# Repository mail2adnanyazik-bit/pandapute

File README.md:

# Pandapute - a mini computer built from scratch

Before you keep reading and find out more about my kickass project, first I want to give credit and a massive thanks to @zsharpminor, or Udo - He's my first friend on Hack Club, a reviewer, and all-around great guy who helped me with this project along every step of the way.
This project would not have been possible without him, so <3 to him :D

## The Inspiration

So, one day I was working on my Split Keyboard project at my makespace, and I saw a friend of mine using a cardputer adv (which is a small, portable esp-based computer - see pic), and was curious.
I asked him what it was, and he showed me, and I gotta say, I was skeptical at first, but then I was blown away - I just had one complaint when I saw the thing :
the keyboard. You see, the original cardputer uses this tiny ass 56-key keyboard, which is 1) too many keys in my opinion, and 2) extremely hard to type on.

So, I decided to make my own, and get funding from Outpost.

## The Features

So, the Pandapute features every single feature the Cardputer has + more !

It has :

- The best ESP32 chip that has wifi and bluetooth capabilities (ESP32-S3-WROOM-1-N16R8)
- an actual **extremely** low profile, compact, built in mechanical 32-key keyboard
- an Audio Jack
- A LiPo battery that will last ages
- a built in speaker
- a microphone
- exposed I2C, GPIO, Power, etc. Pins so you can connect external modules or breakout boards, like a secondary display
- A USB-C port for **both** flashing **and** charging
- a tilt sensor (to do cool stuff)
- a 2.8" display (around twice as big as the cardputer)

## The Build

The Cardputer is built from scratch by me, Panda

It features an entirely custom

### Schematic

#### Power

#### ESP

#### Audio

#### Display

#### Keyboard

#### Peripherals

and

### PCB

to visualize how this will look in real life, here are a few pics ! I only added the important components that you'll actually see, not the encoder chips and stuff :

Now you're probably wondering, will you just carry a PCB around ? OF COURSE NOT. But you know what I'm also not gonna do ?
Put it in some lame ass 3d printed case. That would be boring, inaccurate, and wouldn't feel good in my hands. So ... what's my solution for the

### Case ?

You see, instead of the usual 3d printed stuff, I've decided I'm going to use the full potential of my makespace and make
a custom wood case with a nice finish and accurate measurements after ordering the components, using my local wood workshop.

Another reason for the wood case is inaccuracy - what I mean by that is that some of my components have rather inaccurate measurements - the measurements I have currently on the PCB are only approximations for some components, for example my display :
Since there isn't a prebuilt footprint for this, I had to make my own version which is based on a user-made 3d model approximation of the same component - the downside of this is that it's not accurate.
For the PCB this is rather easy to fix - just order the components first and _then_ adjust the PCB after measuring the components with a digital caliper !

As to how the case will be assembled - it will be made up of 2 parts - One bottom shell which holds the PCB and has holes for the audio jack, USB-C port, and whatever else sticks out the side, and one Top Plate which has holes that the top components that should be exposed can poke through (screen, switches, keyboard, etc.)

To visualize how the entire thing will look, I made a CAD after @zsharpminor (my first friend on Hack Club, was a great help, if you're reading this tysm ! ) said it would be helpful for polish

I first made a model of the Bottom Shell :

Then of the Top part (with cool Panda logo, also thanks to zsharp's feedback - again, tysm for putting up with me zsharp !)

After that for visualization purposes I made an Assembly to show how it will look in the end :

If you want a better more interactive look at this case and how it's built, check out the Onshape document where I made it !

https://cad.onshape.com/documents/acd94843717f517182d6e668/w/23be4fdb216877c251d3e9a3/e/5f36188dd017400931f1858c?renderMode=0&uiState=6a65fce0e255515915538acc

## Firmware

The firmware is a full OS-like environment, not just a bunch of drivers. It runs on the Arduino framework with PlatformIO and gives you a desktop UI, terminal, text editor, file manager, and USB HID keyboard mode.

```
firmware/
├── platformio.ini               # dev + release builds (TFT_eSPI, SdFat)
├── include/
│   ├── config.h                 # all pin definitions
│   ├── kernel.h                 # OS kernel — app management, status bar
│   └── apps.h                   # app function declarations
└── src/
    ├── main.cpp                 # boots hardware + OS, main event loop
    ├── kernel.cpp               # app switching, status bar, event routing
    ├── apps/
    │   ├── desktop.cpp          # home screen — app grid launcher
    │   ├── terminal.cpp         # shell with commands (help, clear, echo, bat, reboot)
    │   ├── editor.cpp           # text editor — cursor, insert/delete, Ln/Col status
    │   ├── files.cpp            # SD card file browser
    │   ├── settings.cpp         # brightness, volume, USB mode toggles
    │   ├── piano.cpp            # keyboard piano — keys 1-8 play notes, octave shift
    │   ├── mic.cpp              # mic level visualizer — real-time bar graph
    │   └── tilt.cpp             # MPU6050 orientation — circle + dot + accel/gyro values
    ├── keyboard/                # 4×8 matrix scanner, debounce, HID keymap
    ├── display/                 # TFT_eSPI wrapper
    ├── audio/                   # I²S output + ES8311 codec + mic input
    ├── touch/                   # XPT2046 SPI touch with calibration
    ├── power/                   # IP5306 battery manager + ADC fallback
    ├── sd_card/                 # SdFat wrapper
    ├── usb_hid/                 # USB HID keyboard — plug in and type
    └── mpu/                     # MPU6050 accelerometer + gyroscope driver
```

#### OS Architecture

The **kernel** manages 8 apps and a persistent status bar. Every keypress is routed to the currently focused app. The loop runs at ~100 Hz:

1. **Keyboard** — matrix scan → debounce → HID keycode lookup
2. **USB HID** — if connected to a computer, sends the same keystrokes
3. **App** — keypress fed to current app's `on_key()` handler
4. **Touch** — polls XPT2046 for touch position
5. **Battery** — reads IP5306 every 10s, shows in status bar
6. **Status bar** — redrawn every 200ms with app name + battery %
7. **Sensors** — MPU6050 and microphone polled by their respective apps

#### Apps

| App      | Icon | What it does                                                     |
| -------- | ---- | ---------------------------------------------------------------- |
| Desktop  | ~    | Grid launcher, arrow keys to navigate, Enter to launch, ESC back |
| Terminal | >    | Shell with `help, clear, echo, bat, apps, reboot`                |
| Editor   | E    | Notepad with cursor movement, insert/delete, modified indicator  |
| Files    | F    | SD card directory listing                                        |
| Settings | S    | Brightness slider (PWM), volume (I²C codec), USB mode toggles    |
| Piano    | P    | 8-key piano (keys 1-8), UP/DN change octave, visual key press    |
| Mic      | M    | Real-time microphone level bar graph, record/pause toggle        |
| Tilt     | T    | 3D orientation circle with dot, live accelerometer/gyro values   |

Pressing **ESC** from any app returns to the Desktop.

#### USB HID

When connected to a computer via USB-C with `-DARDUINO_USB_MODE=1` and `-DARDUINO_USB_CDC_ON_BOOT=1`, the Pandapute shows up as a standard USB keyboard. Everything you type on the mechanical keyboard goes straight to the computer. Modifier keys (Shift, Ctrl, Alt) work too.

#### Building

```bash
cd firmware
pio run -e esp32-s3-dev
pio run -e esp32-s3-dev -t upload
pio device monitor -b 115200
```

Display pins are set in `platformio.ini` via `build_flags`. Touch and SD pins are in `config.h`.

#### Keymap

The keymap in `keyboard/keymap.h` uses standard USB HID keycodes (0x04–0xE7). Modify the `KEYMAP[4][8]` array to match your physical key placement. There are placeholder arrays for `KEYMAP_FN` and `KEYMAP_SYM` layers if you want dual-layer action later.

#### config.h

Single file with every pin, I²C address, and system constant. Change the PCB pinout → edit one file.

### BOM

| #   | Qty | Part                              | Price (€)  | Notes                     |
| --- | --- | --------------------------------- | ---------- | ------------------------- |
| 1   | 1   | ESP32-S3-WROOM-1 N16              | 6.07       | Microcontroller           |
| 2   | 1   | IP5306                            | 1.15       | Charging IC               |
| 3   | 1   | ES8311                            | 3.79       | Audio encoder IC          |
| 4   | 1   | TCA8418RTWR                       | 1.85       | Switch matrix scanning IC |
| 5   | 3   | Tactile switches                  | 9.19       | Power/Boot/etc. switch    |
| 6   | 1   | CMA-4544PF-W                      | 8.29       | Microphone                |
| 7   | 1   | 2000 mAh 3.7V LiPo Battery        | 10.79      | Battery                   |
| 8   | 1   | ILI9341                           | 6.19       | Display                   |
| 9   | 32  | Kailh extreme low profile keycaps | 39.79      | Keycaps                   |
| 10  | 1   | USB-C 2.0 receptacle 16 pin       | 2.09       | USB-C port                |
| 11  | 32  | IN4148                            | 1.05       | Diode                     |
| 12  | 32  | Kailh choc v1 brown switches      | 26.79      | Keyboard switches         |
| 13  | 2   | Blue and green LEDs               | 3.00       | LEDs                      |
| 14  | /   | Resistors from 1 - 100k           | 4.00       | Resistor kit              |
| 15  | 1   | 12 V SPST Switch                  | 2.09       | Switch for battery        |
| 16  | 1   | SKRHABE010                        | 2.59       | 5 way nav switch          |
| 17  | 1   | JST connector kit                 | 3.00       | Connector                 |
| 18  | 1   | PJ-342B                           | 2.69       | 3mm Audio Jack            |
| 19  | 1   | Inductor kit                      | 5.29       | Inductors                 |
| 20  | 1   | MPU6050                           | 4.79       | Tilt sensor               |
| 21  | 1   | 4 Ohm 3 Watt stereo speaker       | 1.79       | Speaker                   |
| 22  | 1   | 32GB SD Card                      | 8.39       | Storage                   |
|     | 1   | **PCB**                           | **140.00** | 191×158mm 4-layer         |
|     | 1   | **Shipping**                      | **40.00**  |                           |
|     |     | **Total**                         | **334.67** |                           |
|     |     | **Total (USD)**                   | **379.89** |                           |

## Why X Tier ?

Although this project was initially supposed to be S-Tier and _much_ more simple than its current version, the idea really
grew on me, and I kept having more and more cool ideas for features I could add, and for some reason I _really_ wanted to outdo the cardputer.
So I put in the effort, watched literal days of videos on differential pairs, PCB design, and looked through countless datasheets just to make this project the best it could possibly be.
It evolved into a complex, extremely cool learning experience and project, not just for me, but for every person at my makespace and on slack who spent hours with me, showing me
what I did wrong (it was a lot), what could be improved (also a lot), and what I did well - A great thanks to all of those people too !

Also, to any reviewers - I hope this project makes the cut for X Tier, and if not, I'll make sure to put in the work to somehow get it there, as it could never survive
on just S Tier.

All in all, I'm extremely happy with what I learned, how much time I put in to this, and how many people contributed to this project.

I couldn't be more proud

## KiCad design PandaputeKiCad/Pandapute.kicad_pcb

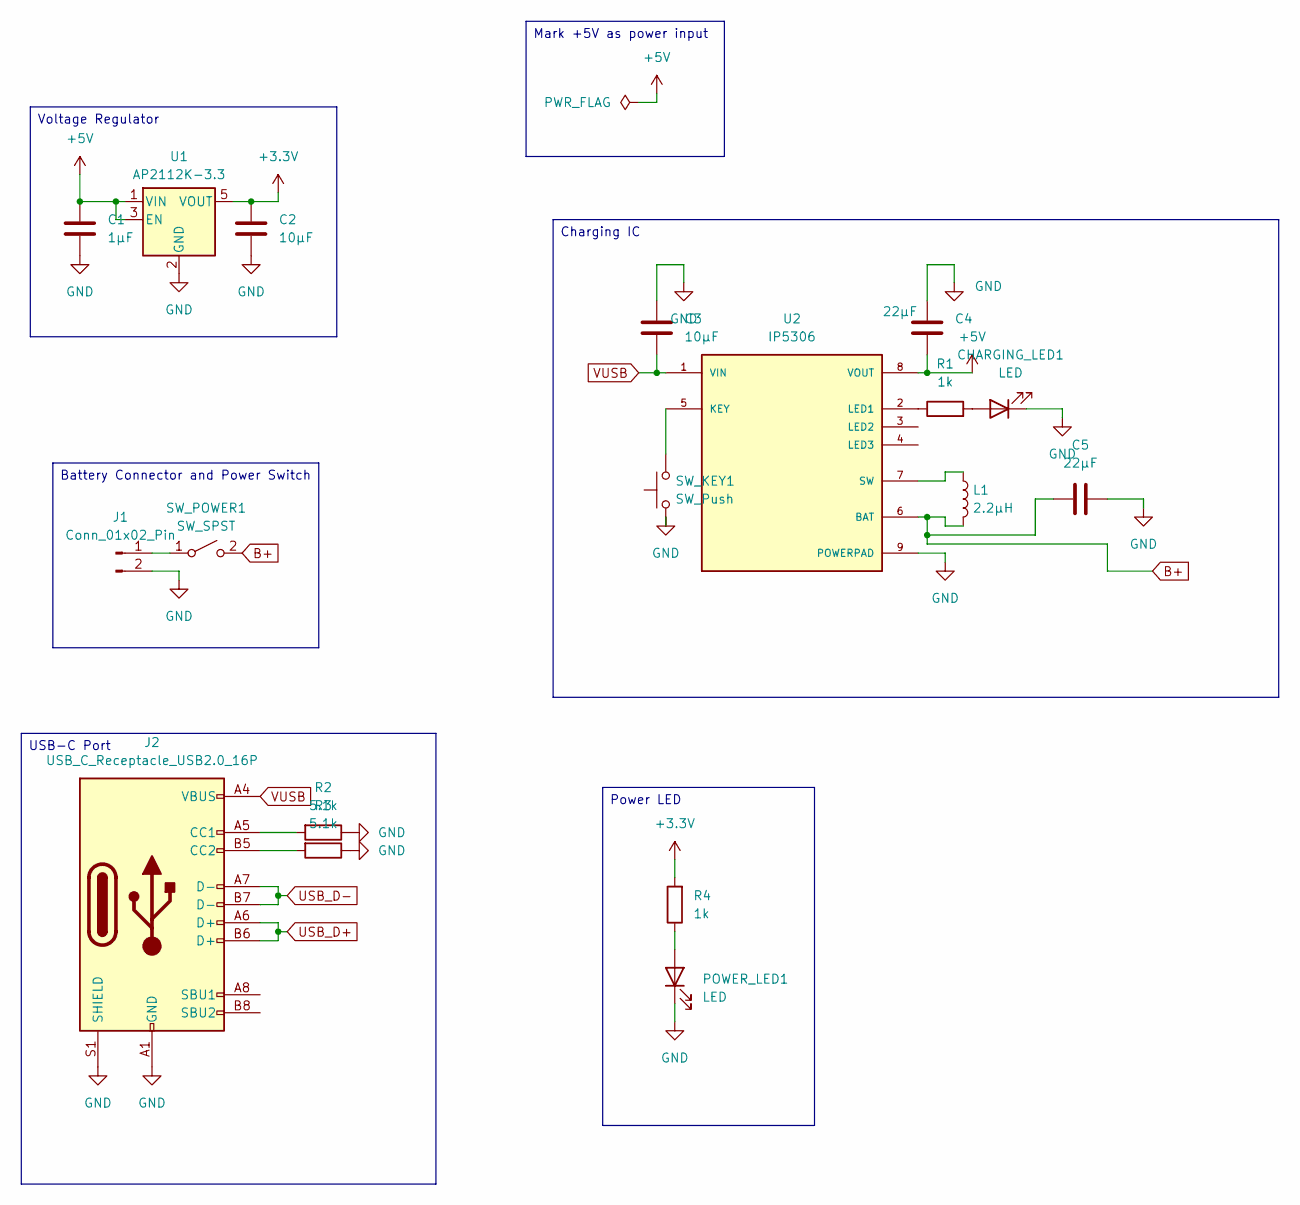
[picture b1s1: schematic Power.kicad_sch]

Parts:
C1: 1µF; C_0603_1608Metric_Pad1.08x0.95mm_HandSolder
C2, C3: 10µF; C_0603_1608Metric_Pad1.08x0.95mm_HandSolder
C4, C5: 22µF; C_0603_1608Metric_Pad1.08x0.95mm_HandSolder
CHARGING_LED1: LED; LED_0805_2012Metric
J1: Conn_01x02_Pin; JST_PH_B2B-PH-K_1x02_P2.00mm_Vertical
J2: USB_C_Receptacle_USB2.0_16P; USB_C_Receptacle_HRO_TYPE-C-31-M-12
L1: 2.2µH; L_1206_3216Metric_Pad1.22x1.90mm_HandSolder
POWER_LED1: LED; LED_0805_2012Metric
R1, R4: 1k; R_0805_2012Metric_Pad1.20x1.40mm_HandSolder
R2, R3: 5.1k; R_0805_2012Metric_Pad1.20x1.40mm_HandSolder
SW_KEY1: SW_Push; SW_PUSH_6mm_H5mm
SW_POWER1: SW_SPST; SW_DIP_SPSTx01_Slide_6.7x4.1mm_W7.62mm_P2.54mm_LowProfile
U1: AP2112K-3.3; SOT-23-5
U2: IP5306; PARTREV 1.31

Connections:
+3.3V: C2.1, R4.2, U1.5 (VOUT); also elsewhere on the board
+5V: C1.1, C4.2, U1.1 (VIN), U1.3 (EN), U2.8 (VOUT); also elsewhere on the board
B+: C5.2, L1.2, SW_POWER1.2 (B), U2.6 (BAT); also elsewhere on the board
GND: C1.2, C2.2, C3.1, C4.1, C5.1, CHARGING_LED1.1 (K), J1.2, J2.A1 (GND), J2.A12 (GND), J2.B1 (GND), J2.B12 (GND), J2.S1 (SHIELD), POWER_LED1.1 (K), R2.1, R3.1, SW_KEY1.1, U1.2 (GND), U2.9 (POWERPAD); also elsewhere on the board
unnamed: CHARGING_LED1.2 (A), R1.2
unnamed: J1.1, SW_POWER1.1 (A)
unnamed: J2.A5 (CC1), R2.2
unnamed: J2.B5 (CC2), R3.2
unnamed: POWER_LED1.2 (A), R4.1
unnamed: SW_KEY1.2, U2.5 (KEY)
unnamed: R1.1, U2.2 (LED1)
unnamed: L1.1, U2.7 (SW)
USB_D+: J2.A6 (D+), J2.B6 (D+); also elsewhere on the board
USB_D-: J2.A7 (D-), J2.B7 (D-); also elsewhere on the board
VUSB: C3.2, J2.A4 (VBUS), J2.A9 (VBUS), J2.B4 (VBUS), J2.B9 (VBUS), U2.1 (VIN)

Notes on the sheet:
Charging IC
Mark +5V as power input
Power LED
USB-C Port
Voltage Regulator
Battery Connector and Power Switch

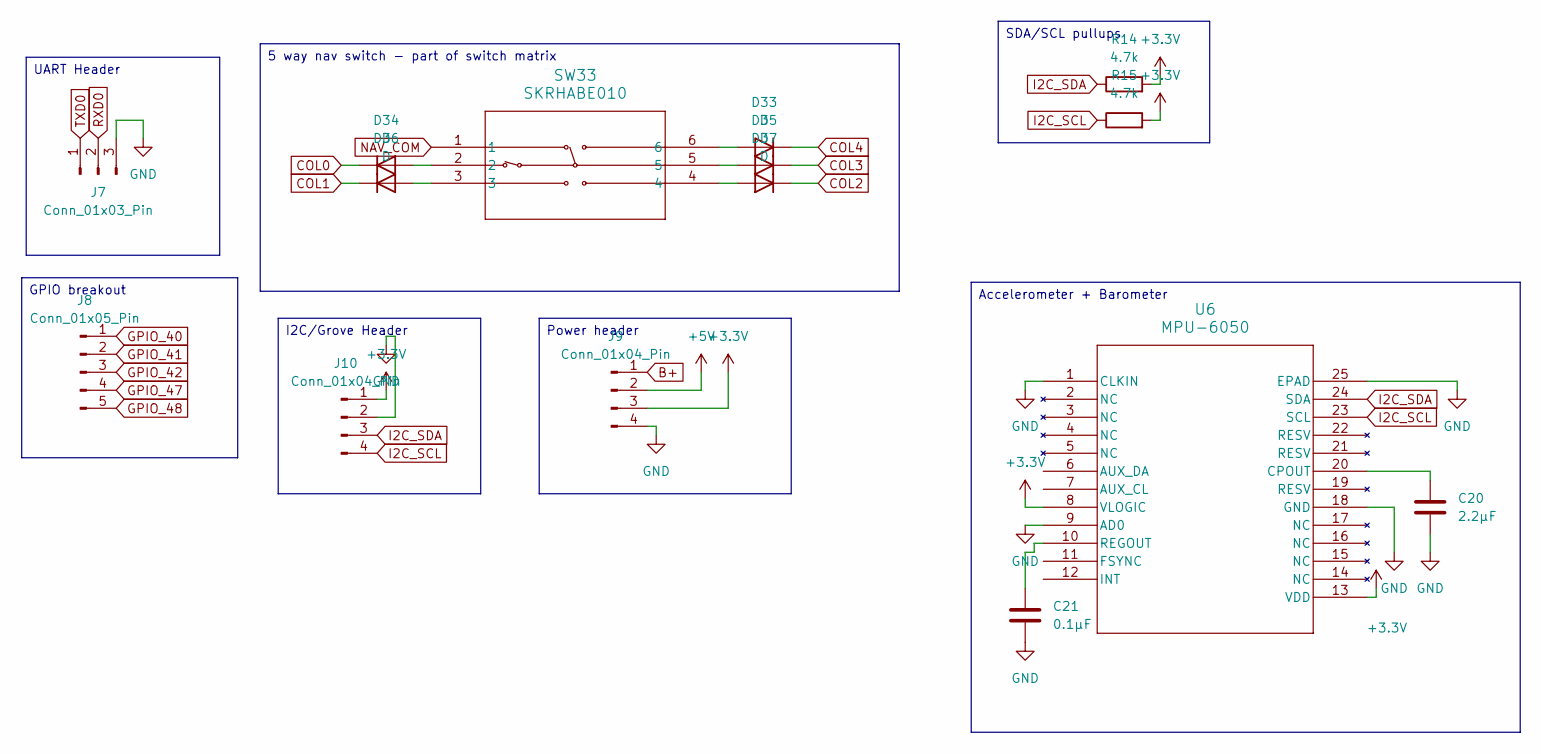
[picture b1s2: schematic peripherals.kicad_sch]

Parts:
C20: 2.2µF; C_0603_1608Metric_Pad1.08x0.95mm_HandSolder
C21: 0.1µF; C_0603_1608Metric_Pad1.08x0.95mm_HandSolder
D33, D34, D35, D36, D37: D; D_DO-35_SOD27_P2.54mm_Vertical_KathodeUp
J7: Conn_01x03_Pin; PinHeader_1x03_P2.54mm_Horizontal
J8: Conn_01x05_Pin; PinHeader_1x05_P2.54mm_Horizontal
J9, J10: Conn_01x04_Pin; PinHeader_1x04_P2.54mm_Horizontal
R14, R15: 4.7k; R_0805_2012Metric_Pad1.20x1.40mm_HandSolder
SW33: SKRHABE010; SKRHABE010_ALPS
U6: MPU-6050; MPU6050

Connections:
+3.3V: J9.3, J10.1, R14.2, R15.2, U6.8 (VLOGIC), U6.13 (VDD); also elsewhere on the board
+5V: J9.2; also elsewhere on the board
B+: J9.1; also elsewhere on the board
COL0: D34.1 (K); also elsewhere on the board
COL1: D36.1 (K); also elsewhere on the board
COL2: D37.1 (K); also elsewhere on the board
COL3: D35.1 (K); also elsewhere on the board
COL4: D33.1 (K); also elsewhere on the board
GND: C20.2, C21.2, J7.3, J9.4, J10.2, U6.1 (CLKIN), U6.9 (AD0), U6.18 (GND), U6.25 (EPAD); also elsewhere on the board
GPIO_40: J8.1; also elsewhere on the board
GPIO_41: J8.2; also elsewhere on the board
GPIO_42: J8.3; also elsewhere on the board
GPIO_47: J8.4; also elsewhere on the board
GPIO_48: J8.5; also elsewhere on the board
I2C_SCL: J10.4, R15.1, U6.23 (SCL); also elsewhere on the board
I2C_SDA: J10.3, R14.1, U6.24 (SDA); also elsewhere on the board
NAV_COM: SW33.1; also elsewhere on the board
unnamed: D33.2 (A), SW33.6
unnamed: D34.2 (A), SW33.2
unnamed: D35.2 (A), SW33.5
unnamed: D36.2 (A), SW33.3
unnamed: D37.2 (A), SW33.4
unnamed: C20.1, U6.20 (CPOUT)
unnamed: C21.1, U6.10 (REGOUT)
RXD0: J7.2; also elsewhere on the board
TXD0: J7.1; also elsewhere on the board

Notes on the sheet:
UART Header
Accelerometer + Barometer
GPIO breakout
5 way nav switch - part of switch matrix
SDA/SCL pullups
Power header
I2C/Grove Header

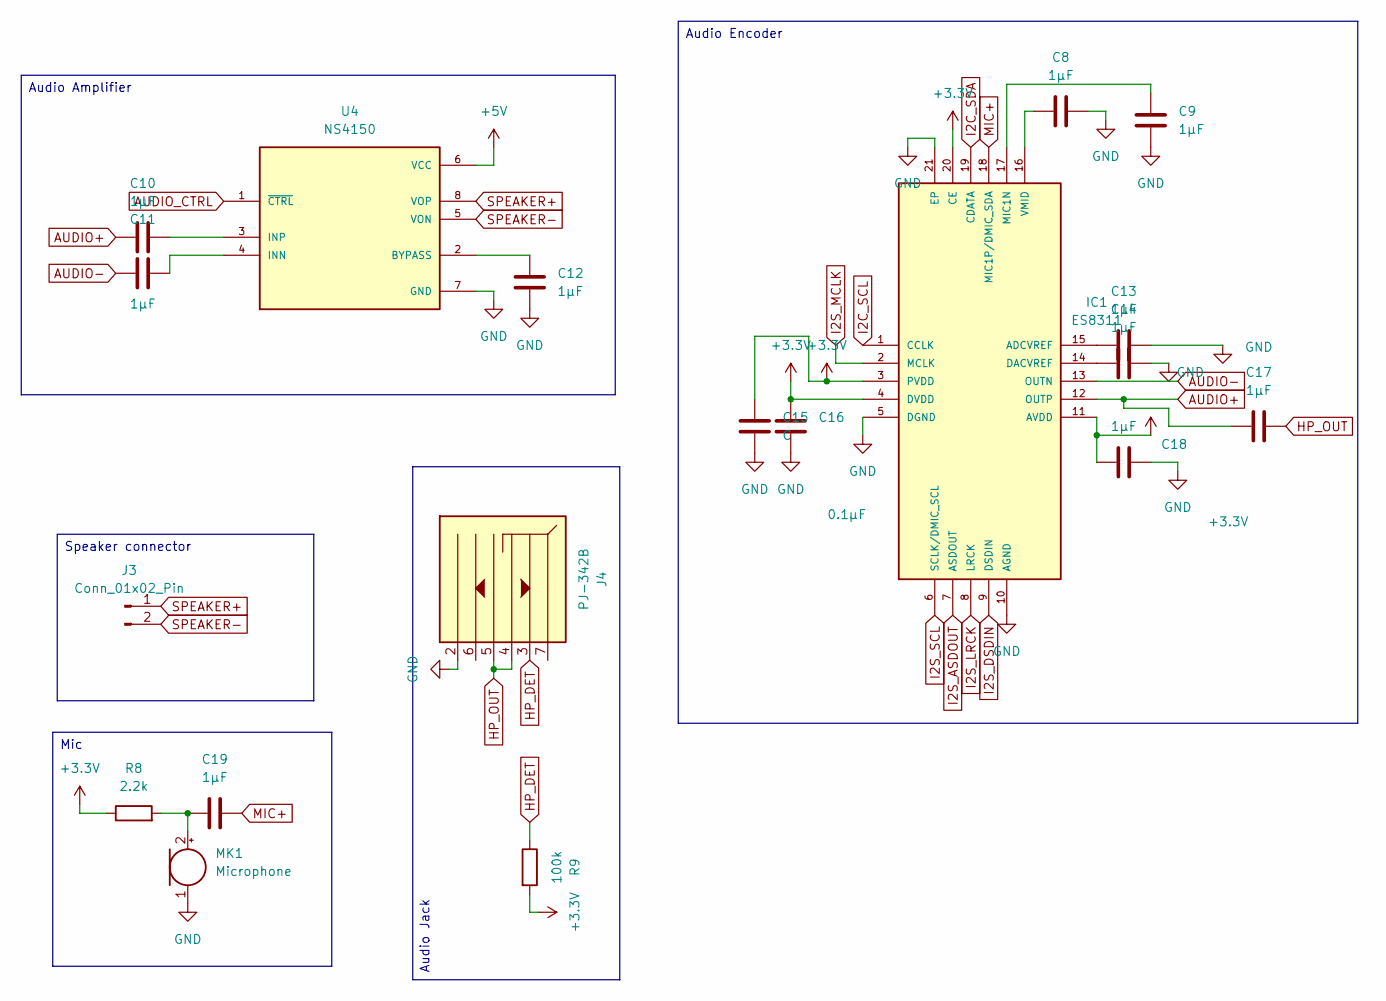
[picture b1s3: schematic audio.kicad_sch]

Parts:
C8, C9, C10, C11, C12, C13, C14, C17, C18, C19: 1µF; C_0603_1608Metric_Pad1.08x0.95mm_HandSolder
C15: C; C_0603_1608Metric_Pad1.08x0.95mm_HandSolder
C16: 0.1µF; C_0603_1608Metric_Pad1.08x0.95mm_HandSolder
IC1: ES8311; MANUFACTURER_PART_NUMBER ES8311
J3: Conn_01x02_Pin; JST_PH_B2B-PH-K_1x02_P2.00mm_Vertical
J4: PJ-342B
MK1: Microphone; MIC_CMA-4544PF-W
R8: 2.2k; R_0805_2012Metric_Pad1.20x1.40mm_HandSolder
R9: 100k; R_0805_2012Metric_Pad1.20x1.40mm_HandSolder
U4: NS4150; PARTREV 1.1

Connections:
+3.3V: C15.1, C16.1, C18.1, IC1.3 (PVDD), IC1.4 (DVDD), IC1.11 (AVDD), IC1.20 (CE), R8.1, R9.2; also elsewhere on the board
+5V: U4.6 (VCC); also elsewhere on the board
AUDIO+: C10.2, C17.1, IC1.12 (OUTP)
AUDIO-: C11.1, IC1.13 (OUTN)
AUDIO_CTRL: U4.1 (~CTRL); also elsewhere on the board
GND: C8.2, C9.2, C12.2, C13.2, C14.2, C15.2, C16.2, C18.2, IC1.5 (DGND), IC1.10 (AGND), IC1.21 (EP), J4.2, MK1.1 (-), U4.7 (GND); also elsewhere on the board
HP_DET: J4.3, R9.1; also elsewhere on the board
HP_OUT: C17.2, J4.4, J4.5
I2C_SCL: IC1.1 (CCLK); also elsewhere on the board
I2C_SDA: IC1.19 (CDATA); also elsewhere on the board
I2S_ASDOUT: IC1.7 (ASDOUT); also elsewhere on the board
I2S_DSDIN: IC1.9 (DSDIN); also elsewhere on the board
I2S_LRCK: IC1.8 (LRCK); also elsewhere on the board
I2S_MCLK: IC1.2 (MCLK); also elsewhere on the board
I2S_SCL: IC1.6 (SCLK/DMIC_SCL); also elsewhere on the board
MIC+: C19.2, IC1.18 (MIC1P/DMIC_SDA)
unnamed: C13.1, IC1.15 (ADCVREF)
unnamed: C14.1, IC1.14 (DACVREF)
unnamed: C9.1, IC1.17 (MIC1N)
unnamed: C8.1, IC1.16 (VMID)
unnamed: C19.1, MK1.2 (+), R8.2
unnamed: C12.1, U4.2 (BYPASS)
unnamed: C11.2, U4.4 (INN)
unnamed: C10.1, U4.3 (INP)
SPEAKER+: J3.1, U4.8 (VOP)
SPEAKER-: J3.2, U4.5 (VON)

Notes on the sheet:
Audio Jack
Audio Amplifier
Mic
Speaker connector
Audio Encoder

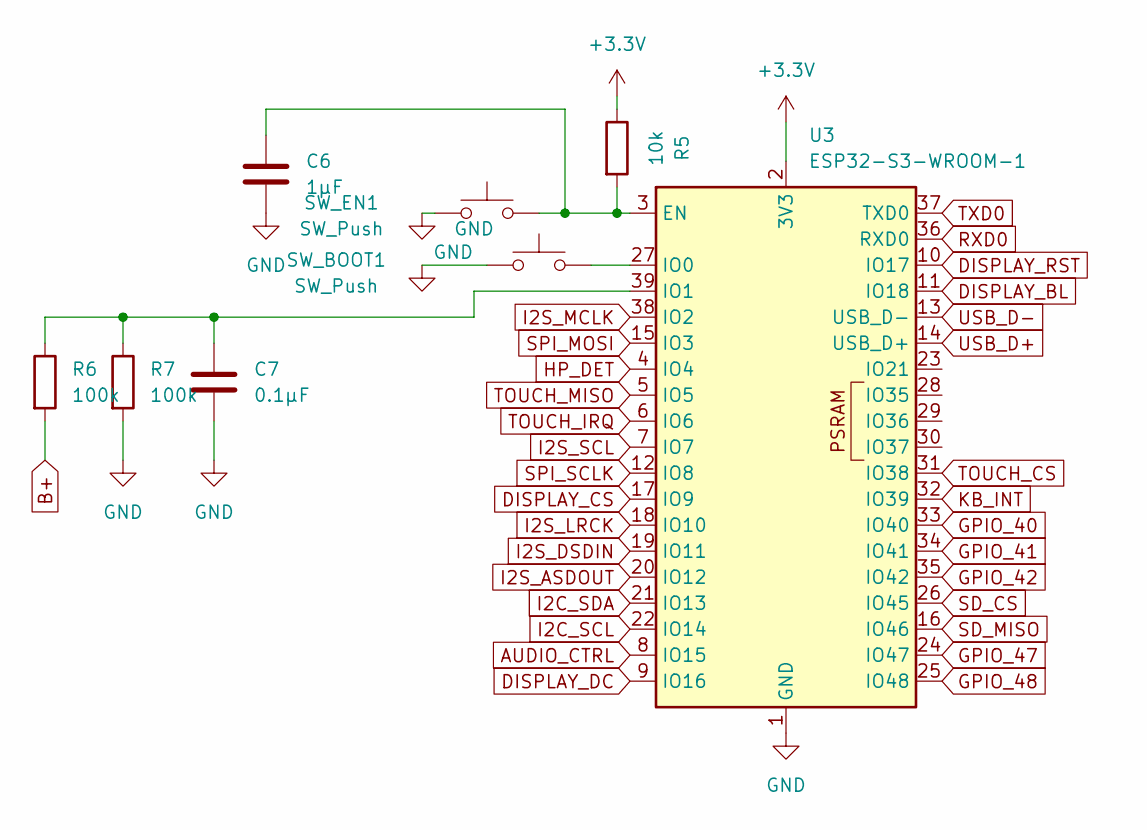
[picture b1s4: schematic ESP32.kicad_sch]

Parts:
C6: 1µF; C_0603_1608Metric_Pad1.08x0.95mm_HandSolder
C7: 0.1µF; C_0603_1608Metric_Pad1.08x0.95mm_HandSolder
R5: 10k; R_0805_2012Metric_Pad1.20x1.40mm_HandSolder
R6, R7: 100k; R_0805_2012Metric_Pad1.20x1.40mm_HandSolder
SW_BOOT1: SW_Push; SW_PUSH_6mm_H5mm
SW_EN1: SW_Push; SW_PUSH_6mm_H5mm
U3: ESP32-S3-WROOM-1

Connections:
+3.3V: R5.1, U3.2 (3V3); also elsewhere on the board
AUDIO_CTRL: U3.8 (IO15); also elsewhere on the board
B+: R6.2; also elsewhere on the board
DISPLAY_BL: U3.11 (IO18); also elsewhere on the board
DISPLAY_CS: U3.17 (IO9); also elsewhere on the board
DISPLAY_DC: U3.9 (IO16); also elsewhere on the board
DISPLAY_RST: U3.10 (IO17); also elsewhere on the board
GND: C6.2, C7.2, R7.2, SW_BOOT1.1, SW_EN1.1, U3.1 (GND), U3.40 (GND), U3.41 (GND); also elsewhere on the board
GPIO_40: U3.33 (IO40); also elsewhere on the board
GPIO_41: U3.34 (IO41); also elsewhere on the board
GPIO_42: U3.35 (IO42); also elsewhere on the board
GPIO_47: U3.24 (IO47); also elsewhere on the board
GPIO_48: U3.25 (IO48); also elsewhere on the board
HP_DET: U3.4 (IO4); also elsewhere on the board
I2C_SCL: U3.22 (IO14); also elsewhere on the board
I2C_SDA: U3.21 (IO13); also elsewhere on the board
I2S_ASDOUT: U3.20 (IO12); also elsewhere on the board
I2S_DSDIN: U3.19 (IO11); also elsewhere on the board
I2S_LRCK: U3.18 (IO10); also elsewhere on the board
I2S_MCLK: U3.38 (IO2); also elsewhere on the board
I2S_SCL: U3.7 (IO7); also elsewhere on the board
KB_INT: U3.32 (IO39); also elsewhere on the board
unnamed: C6.1, R5.2, SW_EN1.2, U3.3 (EN)
unnamed: SW_BOOT1.2, U3.27 (IO0)
unnamed: C7.1, R6.1, R7.1, U3.39 (IO1)
RXD0: U3.36 (RXD0); also elsewhere on the board
SD_CS: U3.26 (IO45); also elsewhere on the board
SD_MISO: U3.16 (IO46); also elsewhere on the board
SPI_MOSI: U3.15 (IO3); also elsewhere on the board
SPI_SCLK: U3.12 (IO8); also elsewhere on the board
TOUCH_CS: U3.31 (IO38); also elsewhere on the board
TOUCH_IRQ: U3.6 (IO6); also elsewhere on the board
TOUCH_MISO: U3.5 (IO5); also elsewhere on the board
TXD0: U3.37 (TXD0); also elsewhere on the board
USB_D+: U3.14 (USB_D+); also elsewhere on the board
USB_D-: U3.13 (USB_D-); also elsewhere on the board

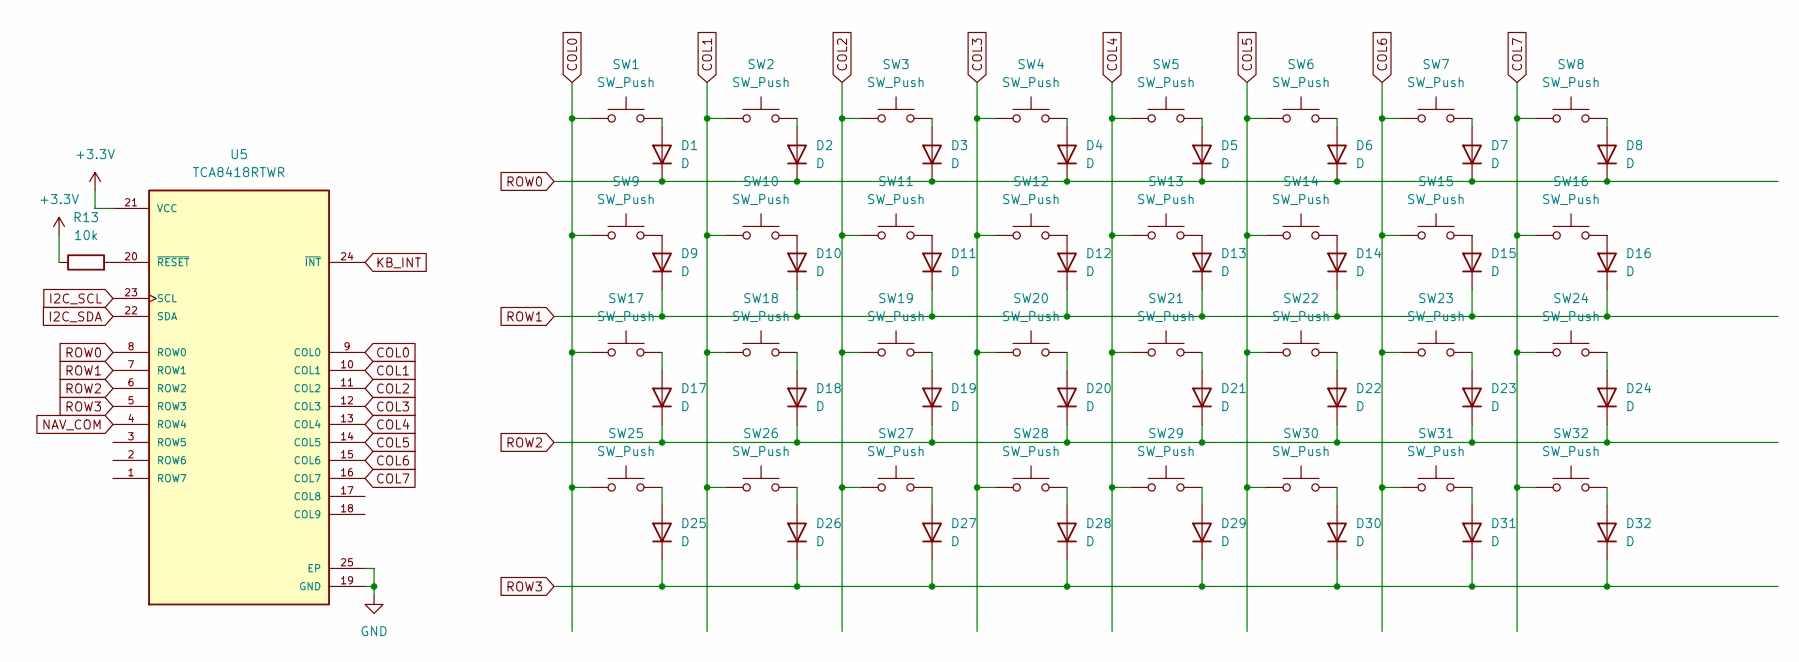
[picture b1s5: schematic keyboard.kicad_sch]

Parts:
D1, D2, D3, D4, D5, D6, D7, D8, D9, D10, D11, D12, D13, D14, D15, D16, D17, D18, D19, D20, D21, D22, D23, D24, D25, D26, D27, D28, D29, D30, D31, D32: D; D_DO-35_SOD27_P2.54mm_Vertical_KathodeUp
R13: 10k; R_0805_2012Metric_Pad1.20x1.40mm_HandSolder
SW1, SW2, SW3, SW4, SW5, SW6, SW7, SW8, SW9, SW10, SW11, SW12, SW13, SW14, SW15, SW16, SW17, SW18, SW19, SW20, SW21, SW22, SW23, SW24, SW25, SW26, SW27, SW28, SW29, SW30, SW31, SW32: SW_Push; SW_choc_v1_1u
U5: TCA8418RTWR; PARTREV G

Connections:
+3.3V: R13.1, U5.21 (VCC); also elsewhere on the board
COL0: SW1.1, SW9.1, SW17.1, SW25.1, U5.9 (COL0); also elsewhere on the board
COL1: SW2.1, SW10.1, SW18.1, SW26.1, U5.10 (COL1); also elsewhere on the board
COL2: SW3.1, SW11.1, SW19.1, SW27.1, U5.11 (COL2); also elsewhere on the board
COL3: SW4.1, SW12.1, SW20.1, SW28.1, U5.12 (COL3); also elsewhere on the board
COL4: SW5.1, SW13.1, SW21.1, SW29.1, U5.13 (COL4); also elsewhere on the board
COL5: SW6.1, SW14.1, SW22.1, SW30.1, U5.14 (COL5)
COL6: SW7.1, SW15.1, SW23.1, SW31.1, U5.15 (COL6)
COL7: SW8.1, SW16.1, SW24.1, SW32.1, U5.16 (COL7)
GND: U5.19 (GND), U5.25 (EP); also elsewhere on the board
I2C_SCL: U5.23 (SCL); also elsewhere on the board
I2C_SDA: U5.22 (SDA); also elsewhere on the board
KB_INT: U5.24 (~INT); also elsewhere on the board
NAV_COM: U5.4 (ROW4); also elsewhere on the board
unnamed: D1.2 (A), SW1.2
unnamed: D2.2 (A), SW2.2
unnamed: D3.2 (A), SW3.2
unnamed: D4.2 (A), SW4.2
unnamed: D5.2 (A), SW5.2
unnamed: D6.2 (A), SW6.2
unnamed: D7.2 (A), SW7.2
unnamed: D8.2 (A), SW8.2
unnamed: D9.2 (A), SW9.2
unnamed: D10.2 (A), SW10.2
unnamed: D11.2 (A), SW11.2
unnamed: D12.2 (A), SW12.2
unnamed: D13.2 (A), SW13.2
unnamed: D14.2 (A), SW14.2
unnamed: D15.2 (A), SW15.2
unnamed: D16.2 (A), SW16.2
unnamed: D17.2 (A), SW17.2
unnamed: D18.2 (A), SW18.2
unnamed: D19.2 (A), SW19.2
unnamed: D20.2 (A), SW20.2
unnamed: D21.2 (A), SW21.2
unnamed: D22.2 (A), SW22.2
unnamed: D23.2 (A), SW23.2
unnamed: D24.2 (A), SW24.2
unnamed: D25.2 (A), SW25.2
unnamed: D26.2 (A), SW26.2
unnamed: D27.2 (A), SW27.2
unnamed: D28.2 (A), SW28.2
unnamed: D29.2 (A), SW29.2
unnamed: D30.2 (A), SW30.2
unnamed: D31.2 (A), SW31.2
unnamed: D32.2 (A), SW32.2
unnamed: R13.2, U5.20 (~RESET)
ROW0: D1.1 (K), D2.1 (K), D3.1 (K), D4.1 (K), D5.1 (K), D6.1 (K), D7.1 (K), D8.1 (K), U5.8 (ROW0)
ROW1: D9.1 (K), D10.1 (K), D11.1 (K), D12.1 (K), D13.1 (K), D14.1 (K), D15.1 (K), D16.1 (K), U5.7 (ROW1)
ROW2: D17.1 (K), D18.1 (K), D19.1 (K), D20.1 (K), D21.1 (K), D22.1 (K), D23.1 (K), D24.1 (K), U5.6 (ROW2)
ROW3: D25.1 (K), D26.1 (K), D27.1 (K), D28.1 (K), D29.1 (K), D30.1 (K), D31.1 (K), D32.1 (K), U5.5 (ROW3)

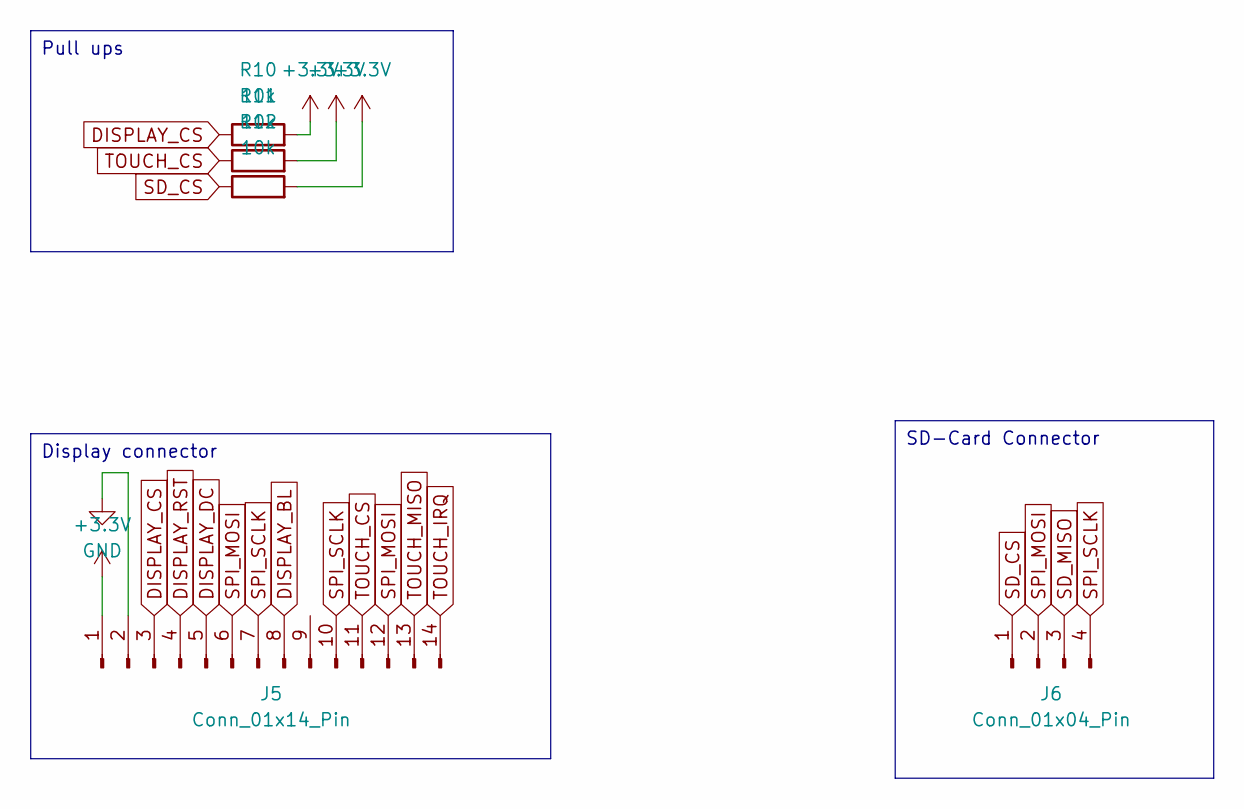
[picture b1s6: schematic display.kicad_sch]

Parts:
J5: Conn_01x14_Pin; PinSocket_1x14_P2.54mm_Vertical
J6: Conn_01x04_Pin; PinSocket_1x04_P2.54mm_Vertical
R10, R11, R12: 10k; R_0805_2012Metric_Pad1.20x1.40mm_HandSolder

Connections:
+3.3V: J5.1, R10.2, R11.2, R12.2; also elsewhere on the board
DISPLAY_BL: J5.8; also elsewhere on the board
DISPLAY_CS: J5.3, R10.1; also elsewhere on the board
DISPLAY_DC: J5.5; also elsewhere on the board
DISPLAY_RST: J5.4; also elsewhere on the board
GND: J5.2; also elsewhere on the board
SD_CS: J6.1, R12.1; also elsewhere on the board
SD_MISO: J6.3; also elsewhere on the board
SPI_MOSI: J5.6, J5.12, J6.2; also elsewhere on the board
SPI_SCLK: J5.7, J5.10, J6.4; also elsewhere on the board
TOUCH_CS: J5.11, R11.1; also elsewhere on the board
TOUCH_IRQ: J5.14; also elsewhere on the board
TOUCH_MISO: J5.13; also elsewhere on the board

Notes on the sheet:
SD-Card Connector
Display connector
Pull ups

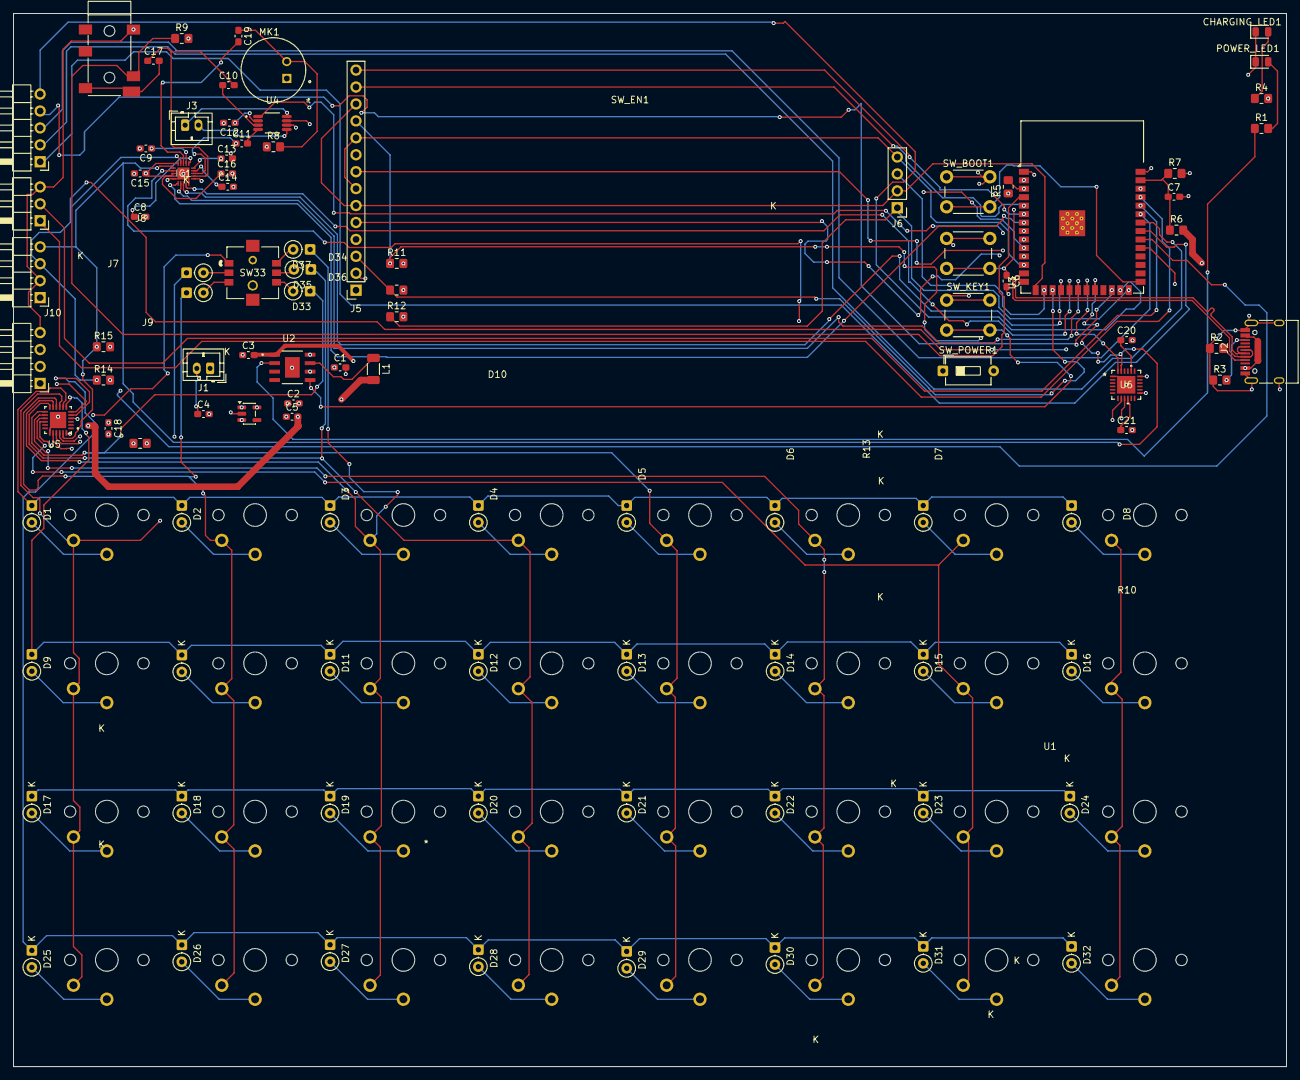
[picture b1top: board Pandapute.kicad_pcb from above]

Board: 4 copper layers, 191.0 x 158.0 mm, 131 parts (0 on the bottom side), 113 nets.

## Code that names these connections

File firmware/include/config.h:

#pragma once

// Display (ILI9341 320x240, SPI)
#define DISPLAY_WIDTH          320
#define DISPLAY_HEIGHT         240
#define DISPLAY_MOSI_PIN       13
#define DISPLAY_SCLK_PIN       12
#define DISPLAY_CS_PIN         10
#define DISPLAY_DC_PIN         11
#define DISPLAY_RST_PIN        14
#define DISPLAY_BL_PIN         15

// Touch (XPT2046, shared SPI bus)
#define TOUCH_CS_PIN           21
#define TOUCH_IRQ_PIN          16

// SD card (shared SPI bus)
#define SD_CS_PIN              7
#define SPI_MISO_PIN           9

// Audio (I2S + ES8311 codec)
#define I2S_BCLK_PIN           17
#define I2S_LRCK_PIN           18
#define I2S_DIN_PIN            19
#define I2S_DOUT_PIN           20
#define I2S_MCLK_PIN           6
#define AUDIO_I2C_SDA_PIN      5
#define AUDIO_I2C_SCL_PIN      4
#define ES8311_I2C_ADDR        0x18

// Power (IP5306)
#define IP5306_I2C_ADDR        0x75
#define POWER_LED_PIN          48
#define CHARGING_LED_PIN       47
#define BAT_ADC_PIN            1
#define BAT_ADC_DIVIDER_R1     100000.0f
#define BAT_ADC_DIVIDER_R2     100000.0f

// Keyboard matrix (direct GPIO scan)
#define KEYBOARD_ROWS          4
#define KEYBOARD_COLS          8
static const uint8_t MATRIX_ROW_PINS[KEYBOARD_ROWS] = {26, 27, 28, 29};
static const uint8_t MATRIX_COL_PINS[KEYBOARD_COLS] = {30, 31, 32, 33, 34, 35, 36, 37};

// Keyboard controller (on-board, not used by firmware)
#define TCA8418_I2C_ADDR       0x34

// USB (native)
#define USB_D_PLUS_PIN         23
#define USB_D_MINUS_PIN        22

// UART
#define UART_TX_PIN            43
#define UART_RX_PIN            44

// Navigation
#define NAV_COM_PIN            45

// System
#define DEBOUNCE_THRESHOLD_MS  5
#define KEYBOARD_POLL_MS       10
#define STATUS_BAR_HEIGHT      20
